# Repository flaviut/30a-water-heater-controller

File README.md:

# 30A Water Heater Controller

This board contains a design for a water heater controller that is good for up to 30A water heaters.

## Warranty

Working with high currents and mains voltages is dangerous. Death from electrical shock & house fires are both real risks with this project.

This project comes with no warranty, and is not examined by or listed by any NRTL. You are solely responsible for determining if it is safe.

## Manufacturing

The latest release contains all the files you need to have this PCB manufactured & 90% assembled by a vendor of your choice. I used JLCPCB.

The defaults are fine. You may wish to ask them to not assemble the thermistor connectors to save a couple bucks.

## Additional BOM

- 1x 100k NTC Temperature Sensor 3950 (2 are supported, but only 1 is useful)
- 1x IRM-05-12 power supply
- 2x J115F21C12VDCS.9
- 4x large wire nuts
- 4x 10AWG UL listed crimp connectors
- 1ft red/1ft black 10AWG coarse-stranded wire
- Suitable electronics enclosure

## Tools

- Soldering iron
- Crimping tool

## Assembly

- Flash ESPHome onto the ESP8266 using the included `esphome.yaml` as a template
- *Turn the circuit breaker off & use a non-contact voltage tester to ensure it is off*
- Cut wire into four 6in pieces; strip one end of each for a crimp connection & the other end for wire nut
- Crimp one end of each wire.
- Solder thermistor header, relays, and power supply. Optionally solder programming header.
- Connect black wires to one relay, red wires to the other
  - one wire to common
  - one wire to normally closed
- Place everything in the enclosure
- Use the wire nuts to connect the pigtails on the common terminals to the mains wiring
- Use the wire nuts to connect the pigtails on the normally closed terminals to the water heater
- Connect one temperature sensor to `100k_HOT`, and feed it out of the enclosure
  - this wire should not be near the mains wiring at any point
- Place one end of the temperature sensor wire down the hole that the top overpressure valve comes out of, and use some paper towels or tape to insulate it in

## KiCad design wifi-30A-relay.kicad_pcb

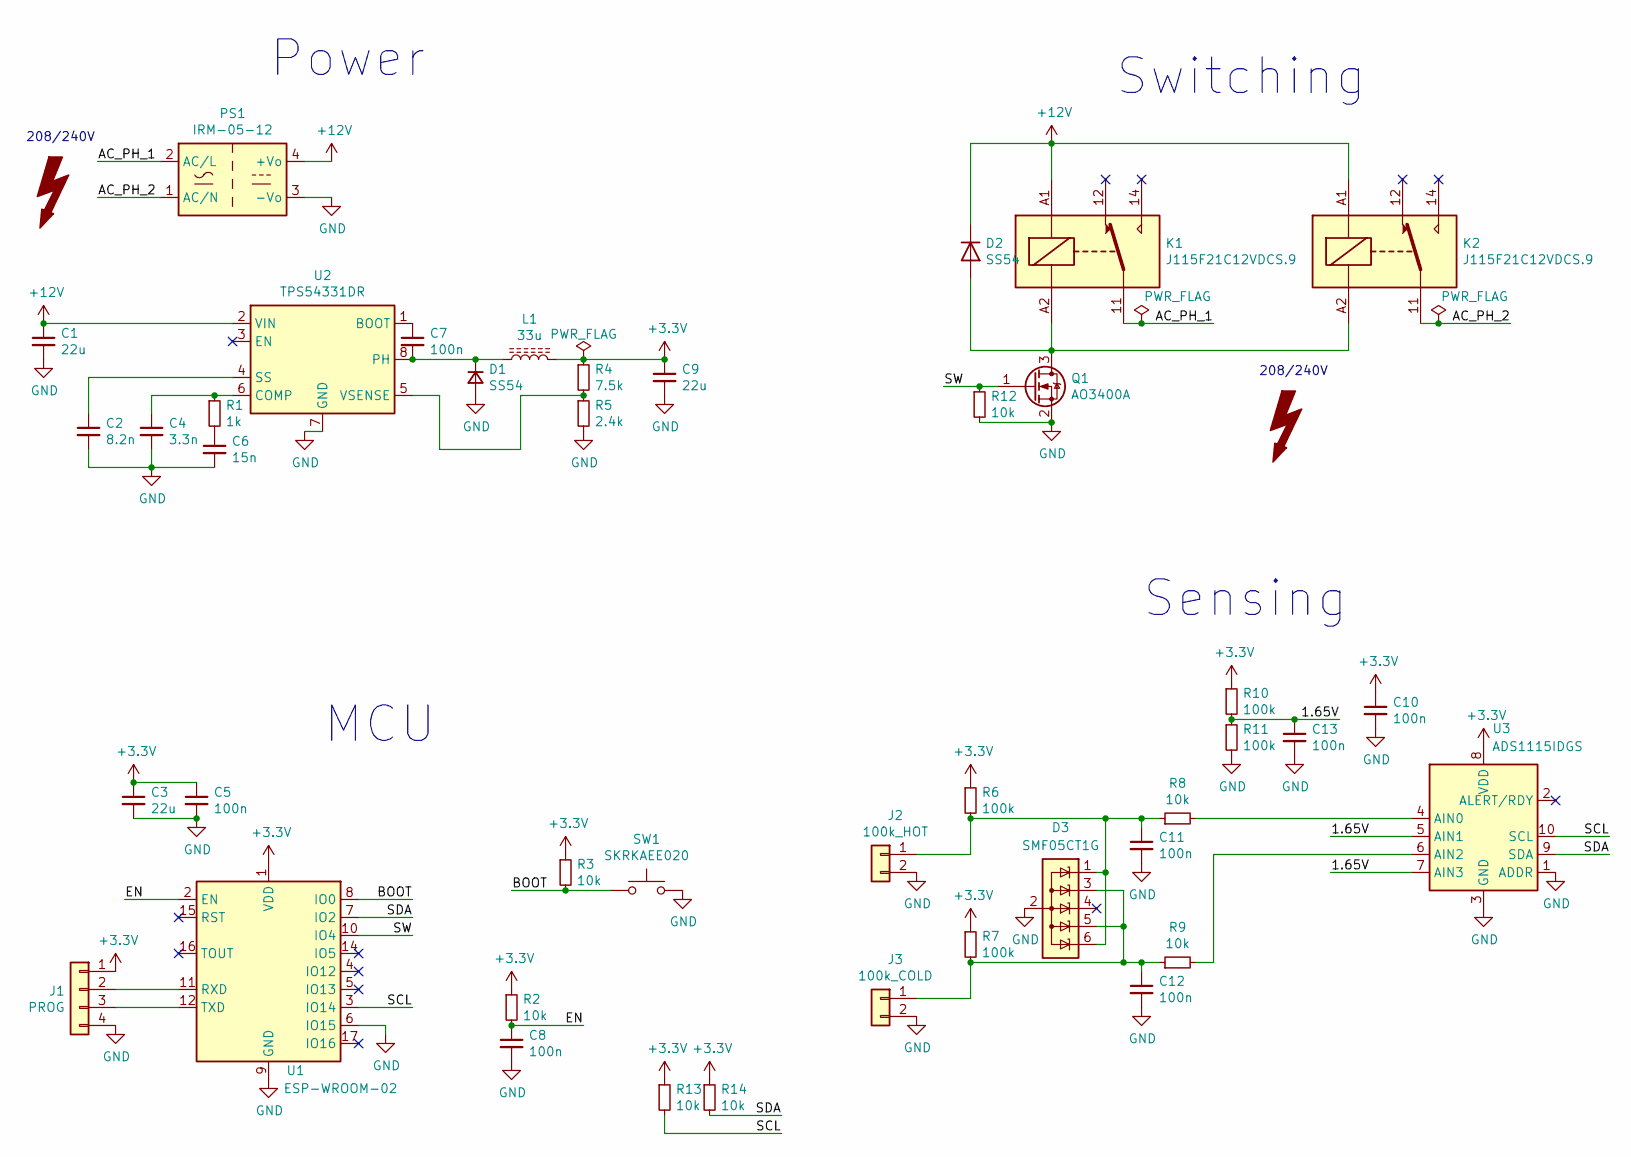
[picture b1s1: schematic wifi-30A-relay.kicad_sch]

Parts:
C1, C3, C9: 22u; C_0805_2012Metric; LCSC C45783
C2: 8.2n; C_0603_1608Metric; LCSC C27920
C4: 3.3n; C_0603_1608Metric; LCSC C1613
C5, C7, C8, C10, C11, C12, C13: 100n; C_0402_1005Metric; LCSC C1525
C6: 15n; C_0603_1608Metric; LCSC C1596
D1, D2: SS54; D_SMA; LCSC C22452
D3: SMF05CT1G; SOT-363_SC-70-6; LCSC C15879
J1: PROG; PinHeader_1x04_P2.54mm_Vertical
J2: 100k_HOT; JST_XH_B2B-XH-AM_1x02_P2.50mm_Vertical; LCSC C2979476
J3: 100k_COLD; JST_XH_B2B-XH-AM_1x02_P2.50mm_Vertical; LCSC C2979476
K1, K2: J115F21C12VDCS.9; Relay_SPDT_CIT-J115F2
L1: 33u; L_TDK_SLF6028; LCSC C149577
PS1: IRM-05-12; Converter_ACDC_MeanWell_IRM-05-xx_THT
Q1: AO3400A; SOT-23; LCSC C20917
R1: 1k; R_0402_1005Metric; LCSC C11702
R2, R3, R8, R9, R12, R13, R14: 10k; R_0402_1005Metric; LCSC C25744
R4: 7.5k; R_0402_1005Metric; LCSC C25918
R5: 2.4k; R_0402_1005Metric; LCSC C25882
R6, R7, R10, R11: 100k; R_0402_1005Metric; LCSC C25741
SW1: SKRKAEE020; SW_Push_SPST_NO_Alps_SKRK; LCSC C115357
U1: ESP-WROOM-02; LCSC C529584
U2: TPS54331DR; SOIC-8_3.9x4.9mm_P1.27mm; LCSC C9865
U3: ADS1115IDGS; TSSOP-10_3x3mm_P0.5mm; LCSC C37593

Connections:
+3.3V: C3.1, C5.1, C9.1, C10.1, J1.1, L1.2, R2.1, R3.1, R4.1, R6.1, R7.1, R10.1, R13.1, R14.1, U1.1 (VDD), U3.8 (VDD)
+12V: C1.1, D2.1 (K), K1.A1, K2.A1, PS1.4 (+Vo), U2.2 (VIN)
/1.65V: C13.1, R10.2, R11.1, U3.5 (AIN1), U3.7 (AIN3)
/AC_PH_1: K1.11, PS1.2 (AC/L)
/AC_PH_2: K2.11, PS1.1 (AC/N)
/BOOT: R3.2, SW1.1, U1.8 (IO0)
/EN: C8.1, R2.2, U1.2 (EN)
/SCL: R13.2, U1.3 (IO14), U3.10 (SCL)
/SDA: R14.2, U1.7 (IO2), U3.9 (SDA)
/SW: Q1.1 (G), R12.1, U1.10 (IO4)
GND: C1.2, C2.2, C3.2, C4.2, C5.2, C6.2, C8.2, C9.2, C10.2, C11.2, C12.2, C13.2, D1.2 (A), D3.2 (A), J1.4, J2.2, J3.2, PS1.3 (-Vo), Q1.2 (S), R5.2, R11.2, R12.2, SW1.2, U1.6 (IO15), U1.9 (GND), U1.13 (GND), U1.18 (GND), U1.19 (GND), U2.7 (GND), U2.9 (GND), U3.1 (ADDR), U3.3 (GND); also elsewhere on the board
unnamed: C2.1, U2.4 (SS)
unnamed: C4.1, R1.1, U2.6 (COMP)
unnamed: C6.1, R1.2
unnamed: C7.1, U2.1 (BOOT)
unnamed: C7.2, D1.1 (K), L1.1, U2.8 (PH)
unnamed 16: C11.1, D3.1 (K), D3.6 (K), J2.1, R6.2, R8.1; also elsewhere on the board
unnamed 17: C12.1, D3.3 (K), D3.5 (K), J3.1, R7.2, R9.1; also elsewhere on the board
unnamed: D2.2 (A), K1.A2, K2.A2, Q1.3 (D)
unnamed: J1.2, U1.11 (RXD)
unnamed: J1.3, U1.12 (TXD)
unnamed: R4.2, R5.1, U2.5 (VSENSE)
unnamed: R8.2, U3.4 (AIN0)
unnamed: R9.2, U3.6 (AIN2)

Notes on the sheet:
Power
MCU
Switching
208/240V
Sensing

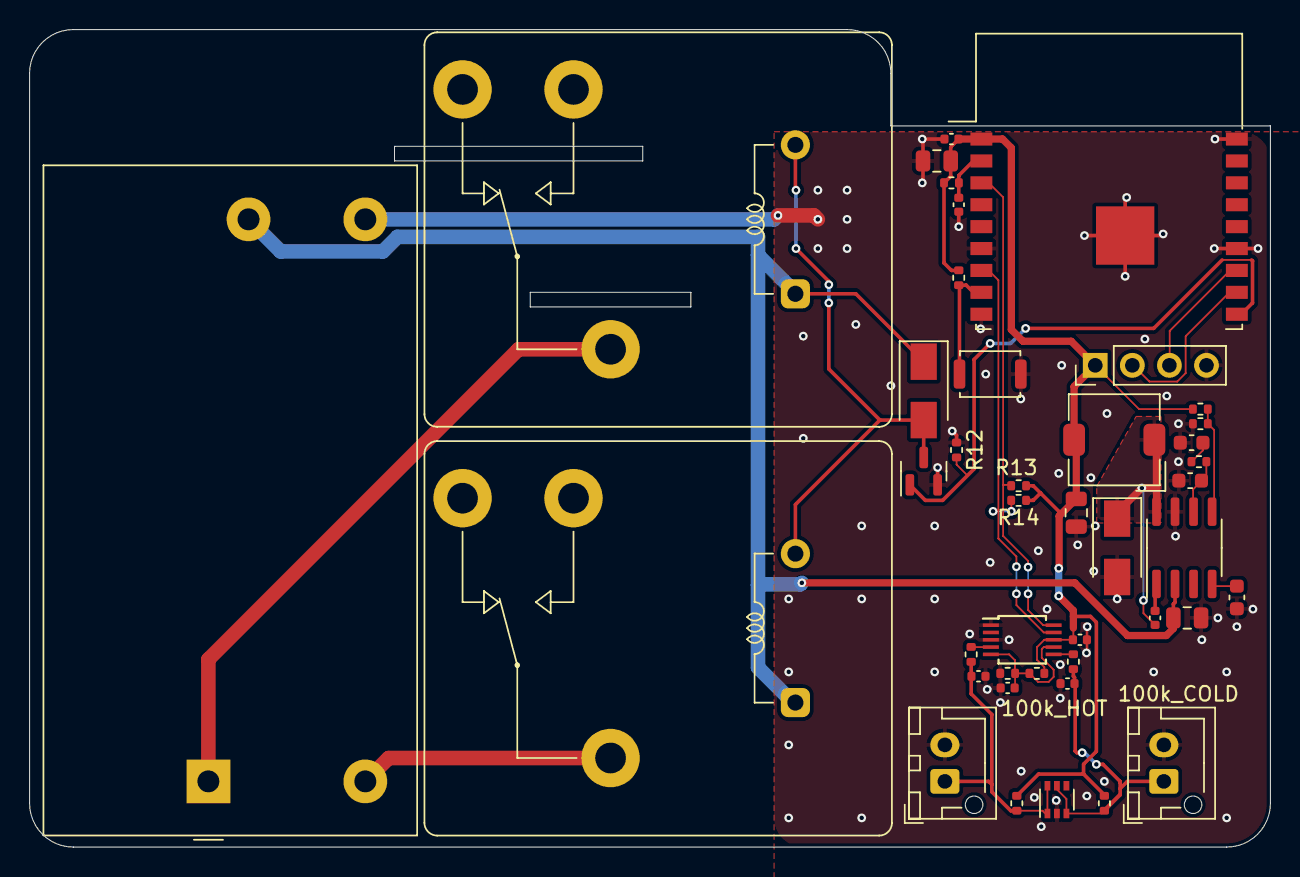
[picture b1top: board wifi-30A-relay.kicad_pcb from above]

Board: 2 copper layers, 85.0 x 56.0 mm, 42 parts (0 on the bottom side), 24 nets.

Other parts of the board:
100k_COLD: 100k_COLD; JST_XH_B2B-XH-AM_1x02_P2.50mm_Vertical
100k_HOT: 100k_HOT; JST_XH_B2B-XH-AM_1x02_P2.50mm_Vertical

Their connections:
GND: 100k_COLD.2, 100k_HOT.2; also elsewhere on the board
unnamed 16: 100k_HOT.1; also elsewhere on the board
unnamed 17: 100k_COLD.1; also elsewhere on the board

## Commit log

2021-08-16 Send off to production
2021-12-31 Fix programming error
2022-01-01 Clean up & add clearance DRC
2022-01-01 Add i2c pull-ups
    Forgotten in previous revisions
2022-01-02 Add more clearance
    This is unnessecary, but double the clearance between the mains &
    low-voltage side to 8mm since we have the room for it.
2023-02-11 Some updates
    Uncommited, been around for a while
2023-02-11 Migrate to new kicad
2023-02-11 Add kibot & fix DRC issues from kicad update
2023-02-11 Fix erc issues
2023-02-11 Replace hand-soldered connectors with JST-XH
    These seem to be the most common connector for the 3950 100k NTC
    connectors found in 3d printers.
2023-02-11 Add esphome config
2023-02-11 Add readme & license, rename files
2023-02-11 Add photo
